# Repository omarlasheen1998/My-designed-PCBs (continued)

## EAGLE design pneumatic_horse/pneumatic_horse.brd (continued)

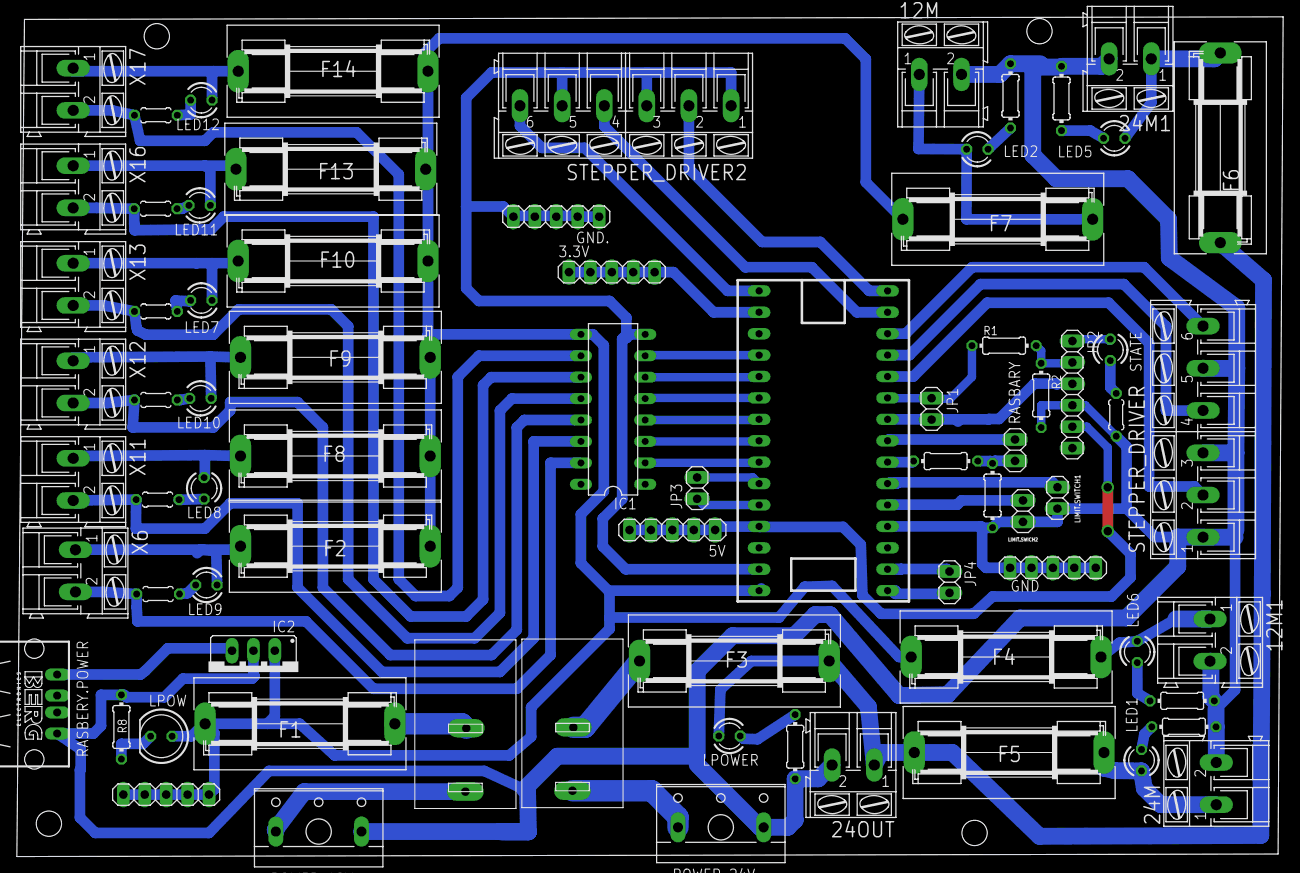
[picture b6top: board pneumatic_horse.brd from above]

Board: 2 copper layers, 150.2 x 99.6 mm, 75 parts (0 on the bottom side), 63 nets.

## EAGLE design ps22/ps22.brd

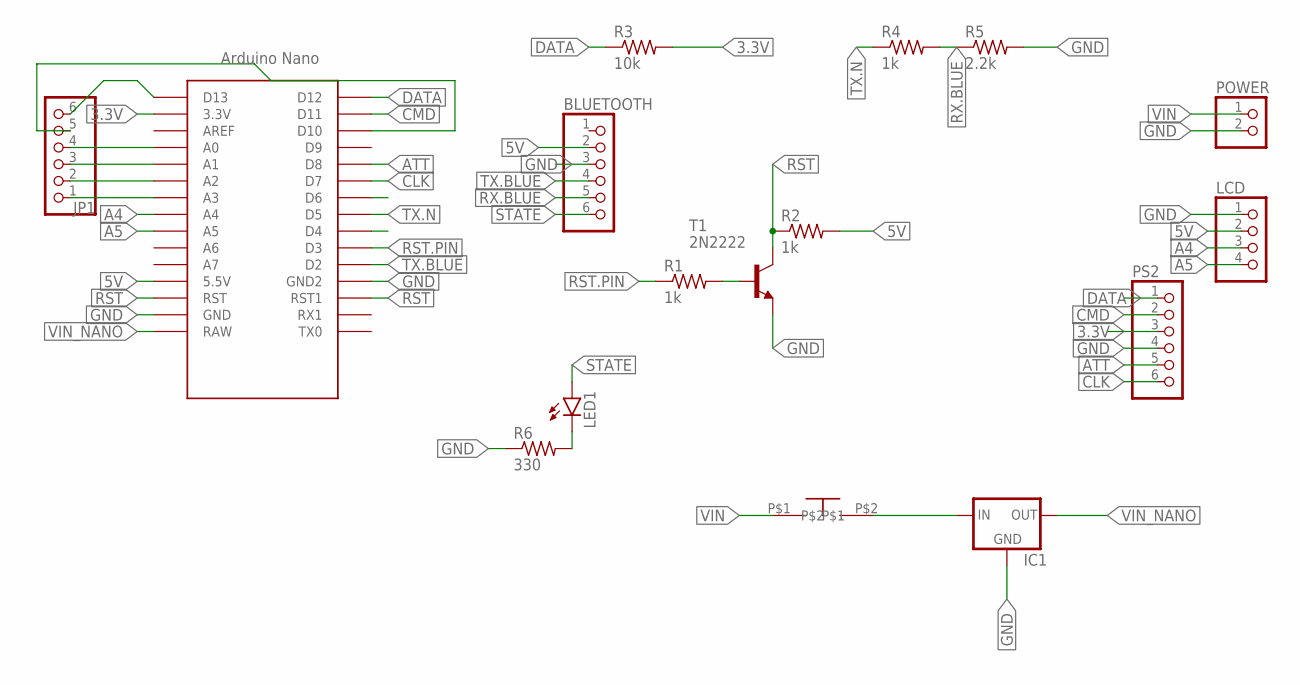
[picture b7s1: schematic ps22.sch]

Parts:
BLUETOOTH: PINHD-1X6; 1X06
IC1: 78XXS
JP1: PINHD-1X6; 1X06
LCD: PINHD-1X4; 1X04
LED1: LED3MM
POWER: PINHD-1X2; 1X02
PS2: PINHD-1X6; 1X06
R1, R2, R4: 1k; 0204/5
R3: 10k; 0204/5
R5: 2.2k; 0204/5
R6: 330; 0204/5
T1: 2N2222; TO18
U$1: NANO
U$2: ON_OFF

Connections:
3.3V: PS2.3, R3.2, U$1.3.3V
5V: BLUETOOTH.2, LCD.2, R2.2, U$1.5V (5.5V)
A4: LCD.3, U$1.A4
A5: LCD.4, U$1.A5
ATT: PS2.5, U$1.D8
CLK: PS2.6, U$1.D7
CMD: PS2.2, U$1.D11
DATA: PS2.1, R3.1, U$1.D12
GND: BLUETOOTH.3, IC1.GND, LCD.1, POWER.2, PS2.4, R5.2, R6.1, T1.1 (E), U$1.GND, U$1.GND1 (GND2)
unnamed: R1.2, T1.2 (B)
unnamed: JP1.1, U$1.A3
unnamed: LED1.K (C), R6.2
unnamed: JP1.2, U$1.A2
unnamed: JP1.3, U$1.A1
unnamed: JP1.4, U$1.A0
unnamed: JP1.6, U$1.D13
unnamed: JP1.5, U$1.D10
unnamed: IC1.IN, U$2.P$2
RST: R2.1, T1.3 (C), U$1.RST, U$1.RST1
RST.PIN: R1.1, U$1.D3
RX.BLUE: BLUETOOTH.5, R4.2, R5.1
STATE: BLUETOOTH.6, LED1.A
TX.BLUE: BLUETOOTH.4, U$1.D2
TX.N: R4.1, U$1.D5
VIN: POWER.1, U$2.P$1
VIN_NANO: IC1.OUT, U$1.RAW

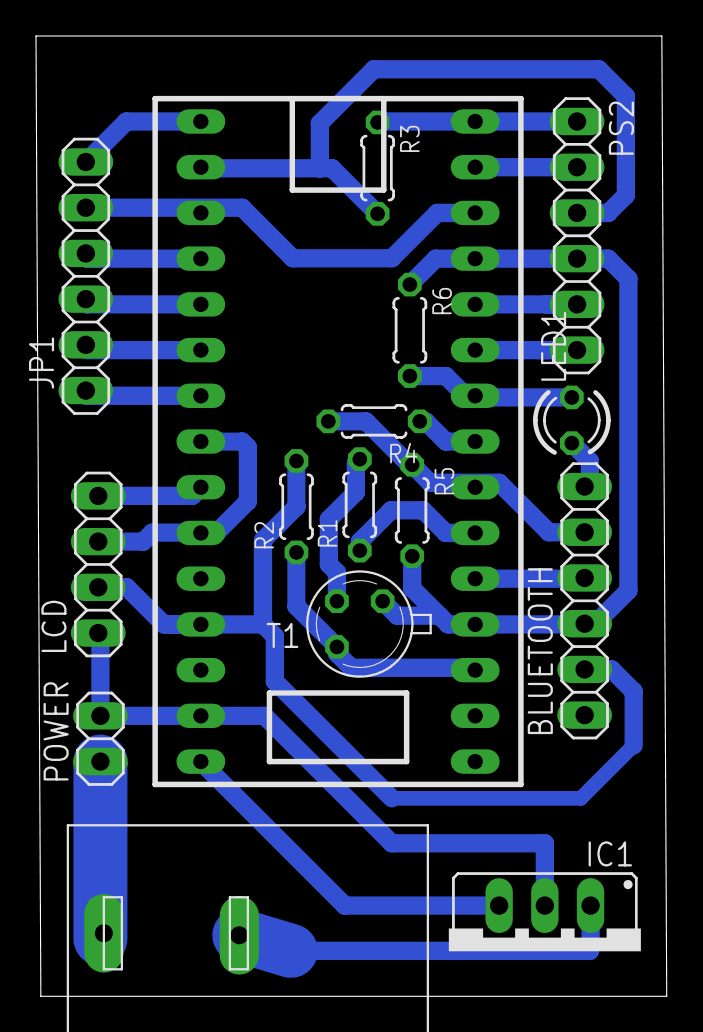
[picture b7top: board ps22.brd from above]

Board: 2 copper layers, 35.0 x 53.4 mm, 16 parts (0 on the bottom side), 26 nets.

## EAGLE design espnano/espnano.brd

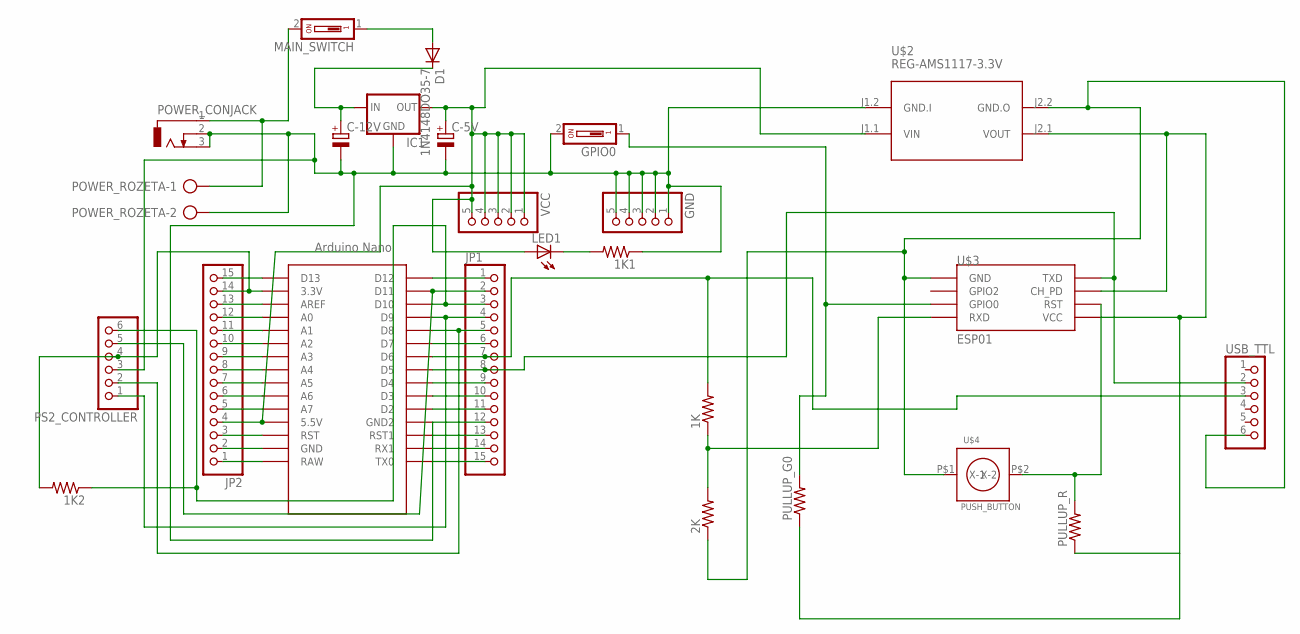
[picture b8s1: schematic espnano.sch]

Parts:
1K, 1K1, 1K2, 2K: R-US_0204/7; 0204/7
C-5V, C-12V: CPOL-EUE2,5-6E; E2,5-6E
D1: 1N4148DO35-7; DO35-7
GND: PINHD-1X5; 1X05
GPIO0: DS01; DS-01
IC1: 78XXS
JP1, JP2: PINHD-1X15; 1X15
LED1: LED5MM
MAIN_SWITCH: DS01; DS-01
POWER_CONJACK: DCJ0303
POWER_ROZETA: AK300/2
PS2_CONTROLLER: PINHD-1X6; 1X06
PULLUP_G0: R-US_0204/7; 0204/7
PULLUP_R: R-US_0204/7; 0204/7
U$1: NANO
U$2: REG-AMS1117-3.3V; REG-AMS1117
U$3: ESP01
U$4: PUSH_BUTTON; DIP2
USB_TTL: PINHD-1X6; 1X06
VCC: PINHD-1X5; 1X05

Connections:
unnamed: JP2.15, U$1.D13
unnamed: JP1.2, PS2_CONTROLLER.5, U$1.D11
unnamed: JP1.4, PS2_CONTROLLER.1, U$1.D9
unnamed: JP1.6, U$1.D7
unnamed: JP1.8, U$1.D5, U$3.TX (TXD), USB_TTL.2
unnamed: C-12V.+, D1.C, IC1.IN
unnamed: JP1.9, U$1.D4
unnamed: JP1.10, U$1.D3
unnamed: JP1.11, U$1.D2
unnamed: 1K1.1, C-5V.-, C-12V.-, GND.1, GND.2, GND.3, GND.4, GND.5, GPIO0.2, IC1.GND, JP1.12, POWER_CONJACK.2, POWER_CONJACK.3, POWER_ROZETA.2, PS2_CONTROLLER.3, U$1.GND1 (GND2), U$2.J1.2 (GND.I)
unnamed: JP1.13, U$1.RST1
unnamed: JP1.14, U$1.RX1
unnamed: JP1.15, U$1.TX0
unnamed: JP2.1, U$1.RAW
unnamed: JP2.2, U$1.GND
unnamed: JP2.3, U$1.RST
unnamed: JP2.5, U$1.A7
unnamed: JP2.6, U$1.A6
unnamed: JP2.7, U$1.A5
unnamed: JP2.8, U$1.A4
unnamed: JP2.9, U$1.A3
unnamed: JP2.10, U$1.A2
unnamed: JP2.11, U$1.A1
unnamed: JP2.12, U$1.A0
unnamed: JP2.13, U$1.AREF
unnamed: JP1.5, PS2_CONTROLLER.2, U$1.D8
unnamed: 1K2.1, JP1.3, PS2_CONTROLLER.6, U$1.D10
unnamed: MAIN_SWITCH.2, POWER_CONJACK.1, POWER_ROZETA.1
unnamed: 1K.2, JP1.7, U$1.D6, USB_TTL.3
unnamed: 2K.1, U$2.J2.2 (GND.O), U$3.GND, U$4.P$1 (X-1), USB_TTL.6
unnamed: PULLUP_G0.1, PULLUP_R.1, U$2.J2.1 (VOUT), U$3.CH_PD, U$3.VCC
unnamed: D1.A, MAIN_SWITCH.1
unnamed: GPIO0.1, PULLUP_G0.2, U$3.GPIO0
unnamed: 1K1.2, LED1.K (C)
unnamed: 1K.1, 2K.2, U$3.RX (RXD)
unnamed: 1K2.2, JP2.14, PS2_CONTROLLER.4, U$1.3.3V
unnamed: JP1.1, U$1.D12
unnamed: PULLUP_R.2, U$3.RST, U$4.P$2 (X-2)
VCC: C-5V.+, IC1.OUT, JP2.4, LED1.A, U$1.5V (5.5V), U$2.J1.1 (VIN), VCC.1, VCC.2, VCC.3, VCC.4, VCC.5

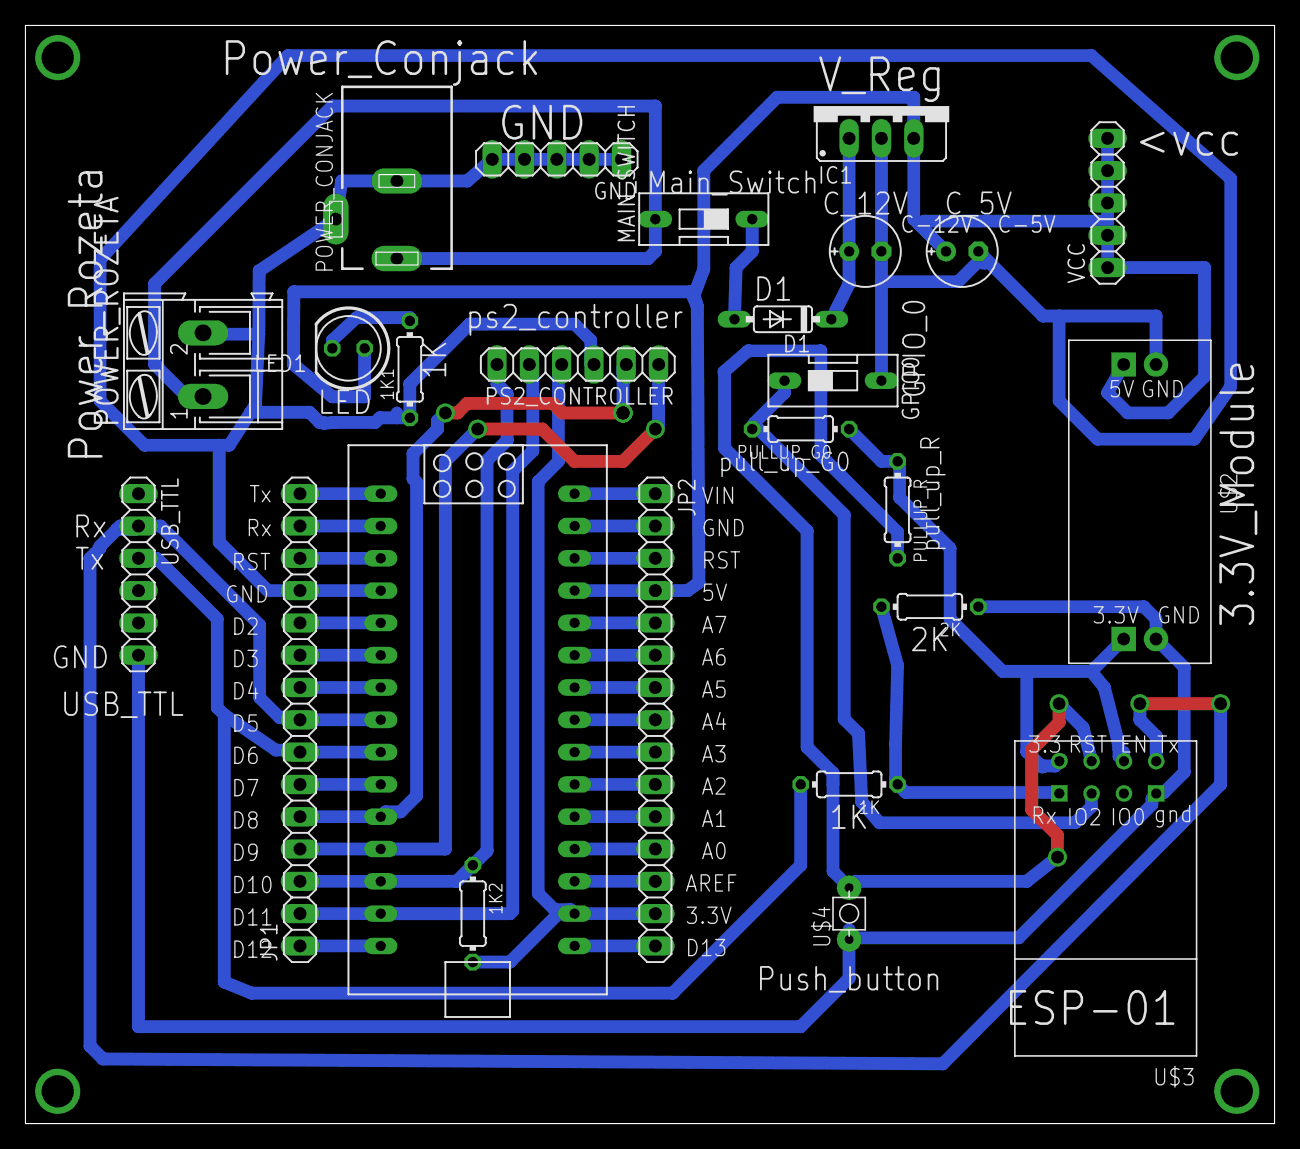
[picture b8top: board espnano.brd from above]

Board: 2 copper layers, 98.2 x 86.3 mm, 25 parts (0 on the bottom side), 39 nets.

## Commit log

2021-04-13 add grad project pcbs
